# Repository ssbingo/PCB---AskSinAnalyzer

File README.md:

# PCB für den AskSinAnalyzer

## Bilder

## Schaltplan

[:arrow_right: Schaltplan](Images/Schaltplan.pdf)

## Platine

[:arrow_right: PCB Gerber](Platine/AskSinAnalyzer V2.0.3.zip)

## Gehäuse

## Aufbau / Stückliste

### Der Aufbau

Bestückung Frontseite<br>

Bestückung Rückseite<br>
Hier gut zu erkennen, der verwendetet ESP32. Das PinOut ist etwas anders.<br>

AskSinnAnalyzer in Betrieb<br>

### Die benötigten Bauteile
| Bauteil | Link |
| --------|------|
|Bauteilliste Reichelt|[:arrow_right: Reichelt](https://www.reichelt.de/my/1678090) |
|Arduinio Pro mini 3.3V | |
|Funkmodul CC1101| |
|Display 2.8 mit SPI|[:arrow_right: Ebay](https://www.ebay.de/itm/322625783359) |

## Hinweise

- :exclamation: Der verwendete ESP32 hatte ein, gegenüber der Beschreibung im Projekt, etwas verändertetes Layout. siehe [Beitrag im Forum](https://homematic-forum.de/forum/viewtopic.php?f=76&t=51161&p=527419#p527456]

## Lizenz

**Creative Commons BY-NC-SA**<br>
Give Credit, NonCommercial, ShareAlike

<br />This work is licensed under a <a rel="license" href="http://creativecommons.org/licenses/by-nc-sa/4.0/">Creative Commons Attribution-NonCommercial-ShareAlike 4.0 International License</a>.

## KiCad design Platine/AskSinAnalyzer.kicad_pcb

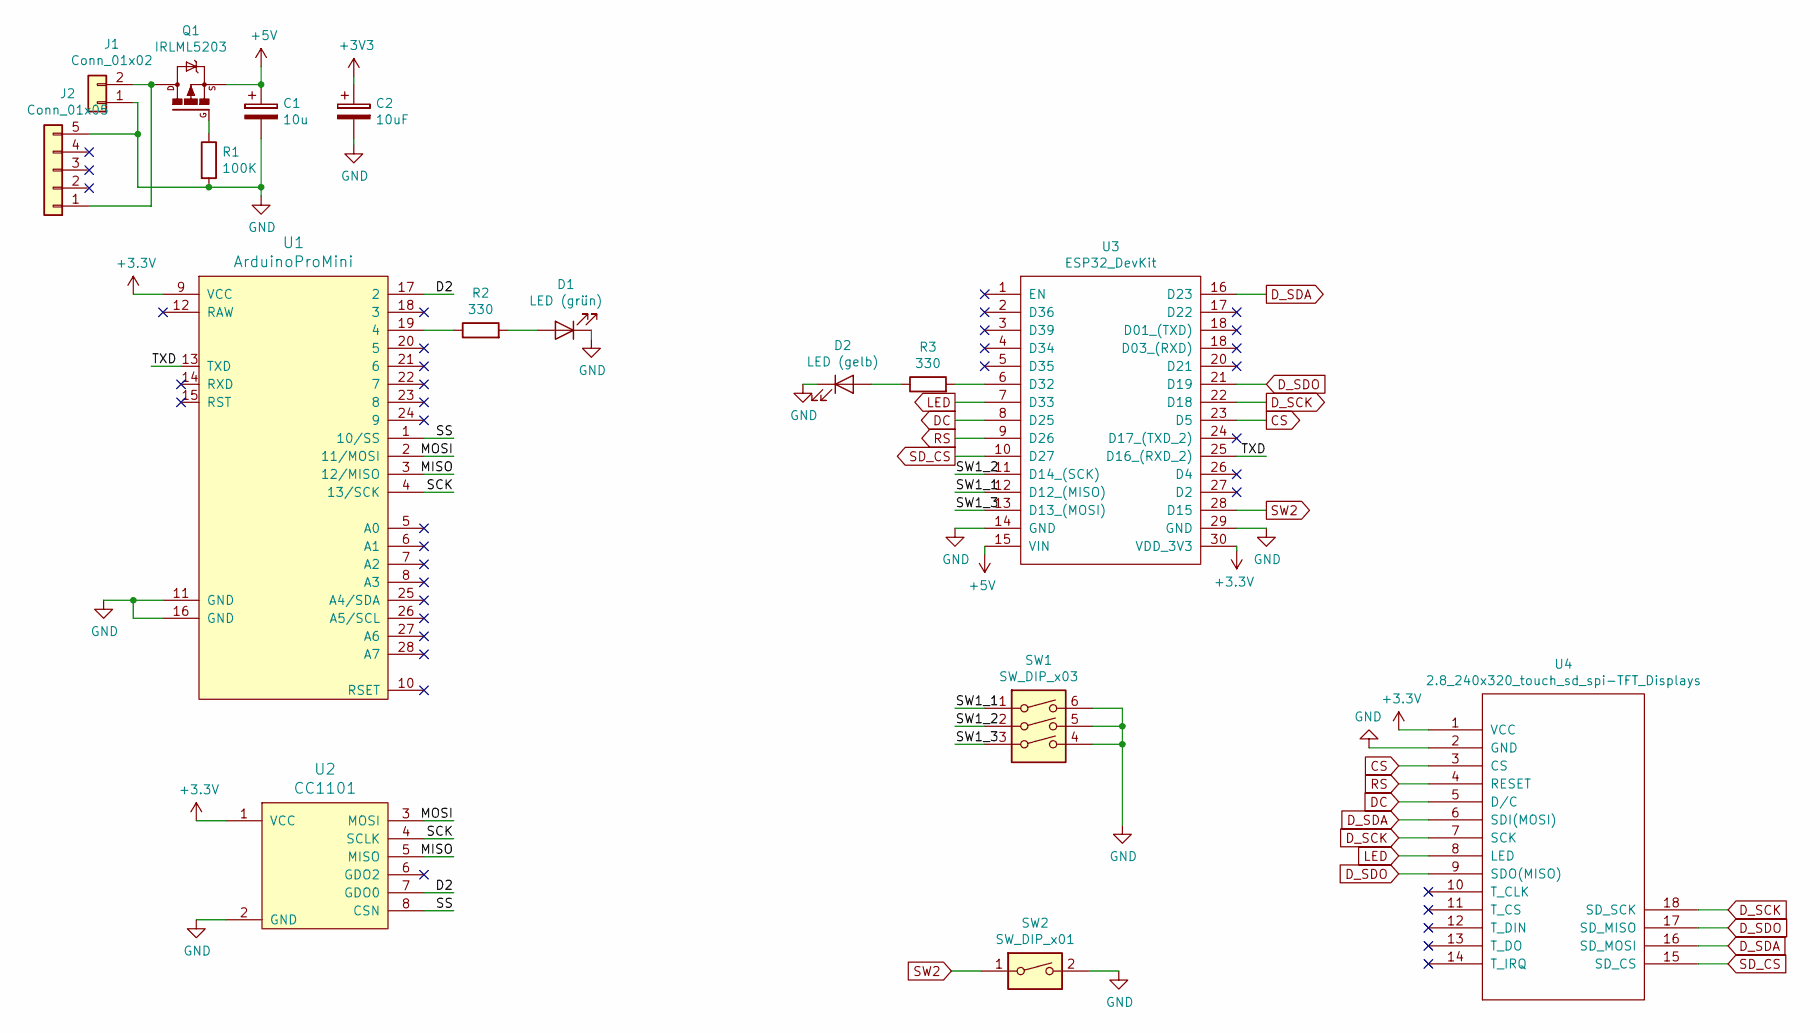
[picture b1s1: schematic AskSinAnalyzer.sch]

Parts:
C1: 10u; CP_Radial_D4.0mm_P1.50mm
C2: 10uF; CP_Radial_D4.0mm_P1.50mm
D1: LED (grün); LED_D3.0mm
D2: LED (gelb); LED_D3.0mm
J1: Conn_01x02; BarrelJack_Horizontal
J2: Conn_01x05; USBMicroBoard
Q1: IRLML5203; SOT-23_Handsoldering
R1: 100K; R_0805_2012Metric_Pad1.15x1.40mm_HandSolder
R2, R3: 330; R_0805_2012Metric_Pad1.15x1.40mm_HandSolder
SW1: SW_DIP_x03; SW_DIP_SPSTx03_Slide_6.7x9.18mm_W7.62mm_P2.54mm_LowProfile
SW2: SW_DIP_x01; SW_PUSH_6mm_H5mm
U1: ArduinoProMini
U2: CC1101
U3: ESP32_DevKit; MODULE_ESP32-DEVKITC-32D_dual
U4: 2.8_240x320_touch_sd_spi-TFT_Displays; 2.8_tft_240x320_touch_sd_spi

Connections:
+5V: C1.1, Q1.2 (S), U3.15 (VIN)
/D2: U1.17 (2), U2.7 (GDO0)
/MISO: U1.3 (12/MISO), U2.5 (MISO)
/MOSI: U1.2 (11/MOSI), U2.3 (MOSI)
/SCK: U1.4 (13/SCK), U2.4 (SCLK)
/SS: U1.1 (10/SS), U2.8 (CSN)
/SW1_1: SW1.1, U3.12 (D12_(MISO))
/SW1_2: SW1.2, U3.11 (D14_(SCK))
/SW1_3: SW1.3, U3.13 (D13_(MOSI))
/TXD: U1.13 (TXD), U3.25 (D16_(RXD_2))
CS: U3.23 (D5), U4.3 (CS)
DC: U3.8 (D25), U4.5 (D/C)
D_SCK: U3.22 (D18), U4.7 (SCK), U4.18 (SD_SCK)
D_SDA: U3.16 (D23), U4.6 (SDI(MOSI)), U4.16 (SD_MOSI)
D_SDO: U3.21 (D19), U4.9 (SDO(MISO)), U4.17 (SD_MISO)
GND: C1.2, C2.2, D1.1 (K), D2.1 (K), J1.1, J2.5, R1.2, SW1.4, SW1.5, SW1.6, SW2.2, U1.11 (GND), U1.16 (GND), U2.2 (GND), U3.14 (GND), U3.29 (GND), U4.2 (GND)
LED: U3.7 (D33), U4.8 (LED)
unnamed: D1.2 (A), R2.2
unnamed: D2.2 (A), R3.1
unnamed: J1.2, J2.1, Q1.3 (D)
unnamed: Q1.1 (G), R1.1
unnamed: R2.1, U1.19 (4)
unnamed: R3.2, U3.6 (D32)
RS: U3.9 (D26), U4.4 (RESET)
SD_CS: U3.10 (D27), U4.15 (SD_CS)
SW2: SW2.1, U3.28 (D15)

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
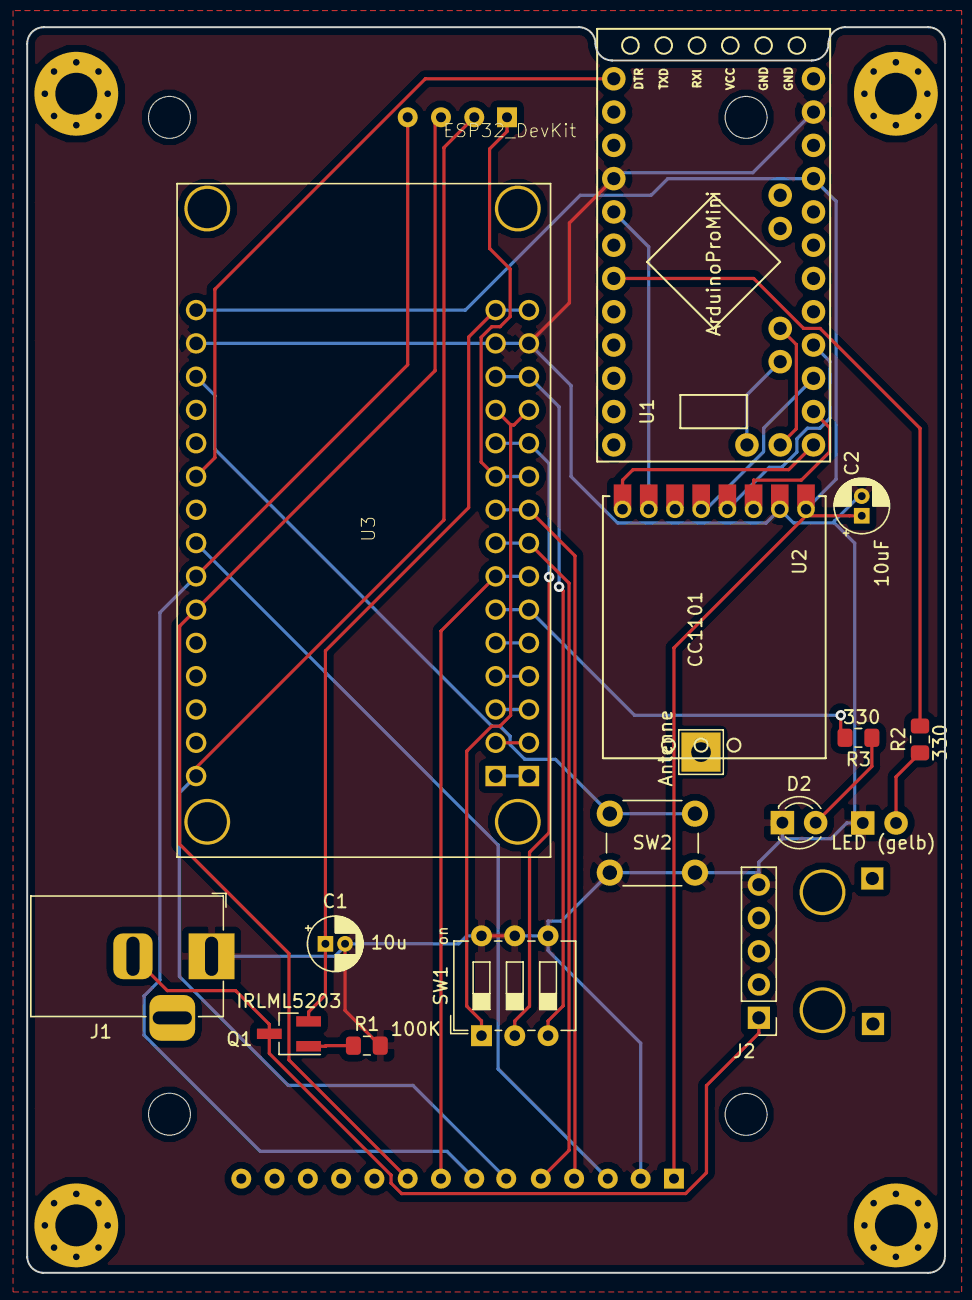
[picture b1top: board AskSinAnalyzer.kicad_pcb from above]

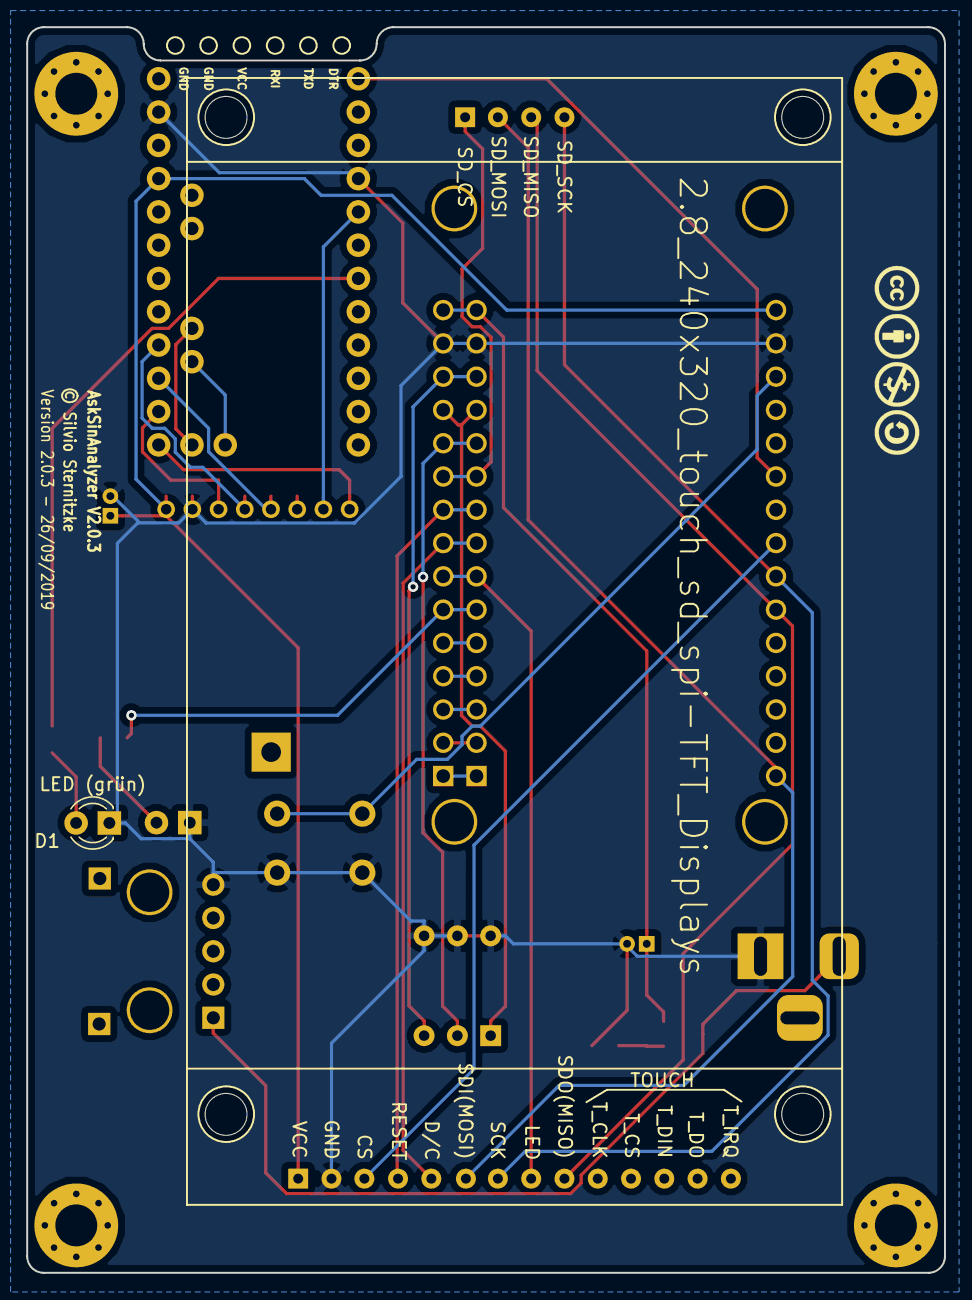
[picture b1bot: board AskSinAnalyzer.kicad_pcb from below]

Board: 2 copper layers, 70.0 x 95.1 mm, 26 parts (2 on the bottom side), 27 nets.

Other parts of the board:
Antenne: TestPoint_THTPad_3.0x3.0mm_Drill1.5mm
Copy: Version 2.0.3 - 26/09/2019; Copyrigth
REF01, REF02, REF03, REF04: MountingHole_3.2mm_M3_Pad_Via
REF020, REF021, REF022, REF23: MountingHole_3.2mm_M3

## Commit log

2020-02-26 Images
2020-02-26 readme.md

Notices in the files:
Platine/AskSinAnalyzer.kicad_pcb:
© Silvio Sternitzke
